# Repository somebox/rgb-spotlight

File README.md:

# RGB Spotlight

Status (2026-11-19): designed and released, not built yet. The driver is released as v2.4, the LED board as v2.0, a second LED board for 3.5 mm LEDs (`led35`) as v1.0, and the sheet-metal housing is in its eighth round. The first order, boards and housing for five lamps, was submitted to JLC on 2026-11-18: it is in JLC's reviews and not paid yet. The lenses were ordered on 2026-11-19. Every figure on this page is calculated or simulated; none is measured. Start with [HANDOVER.md](HANDOVER.md).

Chainable, addressable 3 x 3 W RGB spotlight for 12 V installations: three LEDs, red, green and blue, each behind its own lens, in a square aluminium housing with four barn doors, on a yoke. One lamp is one WS2811 pixel.

The pictures on this page are drawn from the design files. None is a photo.

- **v1** (EasyEDA, one FR4 board) was built but never lit: the PT4115 stages were wired as the wrong kind of buck, and the 74HC04 was unpowered.
- **v2** is a KiCad restart with two boards, an aluminium LED board and an FR4 driver board, and a housing designed around them.

| Document | What's in it |
| --- | --- |
| [HANDOVER.md](HANDOVER.md) | how we got here, decisions, the work remaining |
| [DESIGN.md](DESIGN.md) | requirements, the v1 post-mortem, numbered decisions, circuit, thermal estimate, simulation (§2.7), open items |
| [LAYOUT.md](LAYOUT.md) | the PCBs: floor plans, rules, scripted copper and routing, outline presets, checks |
| [mech/housing/](mech/housing/README.md) | the housing: sheet-metal parts, bought fasteners, assembly order, the scripts that build it and the files to order it from |
| [PRODUCTION.md](PRODUCTION.md) | order files, order checklist (polarity!), harness and bring-up, costs, the orders so far |
| [production/orders/2026-11-16-v2-first/](production/orders/2026-11-16-v2-first/ORDER.md) | the first order: the versions it pins, the parts to buy besides, its events |
| [docs/reviews/](docs/reviews/) | pre-order failure review: findings, bench list, firmware duties |
| [docs/index.html](docs/index.html) | the project's front page: what the lamp is, where it stands, links. GitHub Pages serves `docs/` at <https://somebox.github.io/rgb-spotlight/> |
| [docs/assembly/](docs/assembly/index.html) | assembly guide (HTML, open in a browser): the finished lamp, every part numbered, tools, and 14 steps with pictures drawn from the design files. Written before any part arrived: nothing in it is tried on hardware yet |

## What it does

A high-power, addressable RGB pixel for spotlights and creative lighting. It speaks the WS2811 protocol: 12 V and one data wire come in, and both go on to the next lamp.

The three colours are not mixed inside the lamp. Each LED has its own lens, 12 mm off the lamp's axis, and the colours meet on the wall. Where a door's edge cuts the beam, each colour is cut at a slightly different place, which leaves three colour bands along the shadow. That is the effect the design is after (DESIGN D8, D21–D23). How the bands look is not known until a lamp is built.

- **Optics:** three 20 mm PMMA TIR lenses, 30°, one over each LED.
  - They sit in one printed carrier (MJF PA12), and the hood clamps them by their flanges.
  - Four barn doors on the hood shape the beam, one pair at a time (D21, D22).
  - To compare, lenses of 15° and 45° and with beaded and frosted faces are ordered too, and two taller carriers to try the focus (D27).
- **Housing** ([mech/housing/](mech/housing/README.md)): sheet aluminium from JLCCNC, black powder coat.
  - A 65 mm square shell with vent slots, a back cap, an 84 mm square hood, and a yoke with two knobs.
  - About 94 mm long, 130 with the doors standing; about 0.38 kg (estimated).
  - The cap's back has two cut-outs for the connectors and four M3 threads for a box with a controller and a power supply (D31).
  - The yoke's base has one hole for a ¼ inch screw and two for M4.
- **Cooling:** passive. The LED board lies on a 3 mm aluminium plate. Behind it, eight spacers and four fins on three tie rods take the LEDs' heat to the air that passes the shell's slots.
- **LED board** (aluminium, 1 layer, 50 mm):
  - three XINGLIGHT HD2525 3 W LEDs (R/G/B), spread on a 12 mm-radius ring;
  - each LED on its own heat-spreading copper island;
  - six wire pads around a centre hole for the harness;
  - turned 45° in the housing, so each LED has its own height and its own place from left to right (D23).
- **Driver board** (FR4, 2 layers, 50 mm), on polyamide standoffs behind the fins, about 54 mm behind the LED board:
  - WS2811 pixel controller;
  - three PT4115 constant-current bucks (455 mA each);
  - level shifter on DIN, with a clamp for a feed voltage on the data pin (D28, D29, D34); Schmitt inverter for the PWM polarity;
  - 78L05 logic rail; TVS on the 12 V input.
- **Harness:** three wire pairs from the LED board through the 12 mm bore down the middle of the plate, spacers and fins, each on its own JST XH 2-pin plug (D33).
- **`led35`:** the LED board with pads for 3.5 mm LEDs, bought bare to try other colours on (D35).

The numbers are the assembly guide's part numbers: shell 1, cap 2, hood 3, plate 6, fins 7, spacers 8, carrier 9, LED board 10, driver 11, lenses 12, LED leads 13, tie studs 15, standoffs 18.

The LED board is drawn with a green mask; the ordered ones are white.

## Electrical specs

- **Supply:** 12 V (the PT4115 regulates down to about 6 V at the end of a chain)
- **Data:** WS2811 protocol, 800 kHz, single wire; 3.3 V or 5 V at DIN
- **LED current:** about 455 mA per channel (`I = 0.1 V / 0.22 Ω`); LEDs rated 1 A / 3 W
- **Full white:** 5.0 W, 0.42 A at 12 V per light (simulated, DESIGN.md §2.7); drivers about 80 % efficient
- **Chaining:** JST XH connectors (3 A) pass 12 V/GND through: up to 5 lights per 12 V feed, 2.2–2.6 A, with a 3 A fuse at the supply end (DESIGN.md §2.4, D14, D15). Use a 36 W supply for 4 lights and 60 W for 5, and add a feed per group after that.
- **Heat:** about 2.7 W in the LED board, which goes into the housing's heat plate and fins. About 0.9 W in the driver, mostly in the three Schottky diodes. See DESIGN.md §2.6–2.7.
- **Dimming:** brightness follows the 8-bit level within 5 % above 20 % and within 20 % down to 5 %. The lowest few levels are unreliable (DESIGN.md §2.7).
- **12 V on the data pin** (a mis-crimped cable, or the plug mated at an angle; review R6), simulated with up to 15 V there (D28, D29, `sim/results/data_cable.txt`). On the bench list.
  - With the light powered as well: the 5 V rail stays at 5.0 V and the level shifter's input at 5.43 V or less.
  - With the 12 V and data wires swapped, the light has no feed and the data pin alone holds the 5 V rail up: 2.9–3.5 V with 12 V on the pin, 3.7–4.4 V with 15 V. The level shifter's input stays at 4.84 V or less.
- **Firmware:** FastLED's `WS2811` (800 kHz) fits the WS2811's timing. ESPHome needs its timing set by hand (the review's firmware duties). WLED hasn't been checked. None of it has run on a lamp yet.

## Connections

| Connector | Where | Pins |
| --- | --- | --- |
| J1 IN | driver, back (JST XH 3, vertical) | 1 `12V`, 2 `DATA`, 3 `GND` |
| J2 OUT | driver, back (JST XH 3, vertical) | 1 `12V`, 2 `DATA`, 3 `GND` |
| J3 / J4 / J5 LED | driver, front (JST XH 2, vertical): red, green, blue | 1 `+`, 2 `-` |
| TP1–TP6 | LED board, around the centre hole | `R+` `R-` `G+` `G-` `B+` `B-`; solder the wires here, a pair to each socket |

J1 and J2 share one pin order, so chain with pin-1-to-pin-1 cables. v1 had J2 mirrored. In the housing, both are reached through the cap's cut-outs.

1. Connect the controller's data to J1 pin 2 of the first light, and +12 V / GND to pins 1 / 3. Keep controller and power grounds common.
2. Chain J2 of one light to J1 of the next.
3. Twist each colour's LED pair in the harness.

## Project layout

- `boards/led/`, `boards/driver/`: KiCad 10 projects. Schematics come from `scripts/sch_led.py` / `scripts/sch_driver.py`; boards from `scripts/make_led_pcb.sh` / `scripts/make_driver_pcb.sh`.
- `boards/led35/`: the LED board with pads for 3.5 mm LEDs (DESIGN D35), bought bare; `scripts/sch_led.py led35` and `scripts/make_led_pcb.sh led35`.
- `lib/`: project symbols, footprints and 3D models (`scripts/make_lib.py`).
- `scripts/`: generators and checks (`netcheck.py`, `ratsnest.py`, `make_previews.sh`, `make_fab.sh`); `pcbkit.toml` sets up pcb-kit's release and production record. The shared parts (schematic builder, silkscreen placer, DRC/ERC/board checks, previews, JLC fab files, ngspice runner) come from [pcb-kit](https://github.com/somebox/pcb-kit): `uv tool install -e ~/src/pcb-kit && pcbkit link`.
- `mech/housing/`: the housing as CadQuery scripts (`sheet.py`, then `round2.py` to `round8.py`, each changing the round before), its checks, and the STEP files and drawings to order from (`order6/`, `order7/`, `order8/`). Its [README](mech/housing/README.md) has the parts, the fasteners and the rebuild commands.
- `releases/<board>/v<version>/`: a release's order files and its frozen KiCad project, written by `pcbkit release` and never rewritten.
- `production/orders/<date>-<what>/`: an order's `order.toml` and the ORDER.md that `pcbkit production` writes from it.
- `sim/`: ngspice simulations of one LED channel (`channel.py`) and of the data link between two lights (`data_cable.py`), and the review's worst-case numbers (`worst_case.py`); tables and plots in `sim/results/`.
- `docs/previews/<board>/`: schematic PDF, board PNGs, 3D renders. `docs/previews/outline-presets.png` compares the board outline options.
- `docs/assembly/`, `docs/index.html`: the assembly guide and the front page. The guide's pictures come from `mech/housing/assembly_views.py`.
- **Board outline:** everything sits in a 50 mm core. The edge is a preset, `disc50` (current, and what the housing takes), `disc55`, `disc60` or `tabs3` (screw tabs). Change it with `scripts/set_outline.py`; see LAYOUT.md.
- `archive/v1-easyeda/`: the v1 EasyEDA exports, a KiCad import of the v1 board, its as-built netlist and the bodge guide.

Checks, previews and a release:

```bash
pcbkit erc boards/driver/driver.kicad_sch && python3 scripts/netcheck.py
pcbkit drc boards/driver/driver.kicad_pcb --save && pcbkit check boards/driver/driver.kicad_pcb
scripts/make_previews.sh all
pcbkit release --dry-run                                    # then pcbkit release: versioned order files in releases/ (PRODUCTION.md)
python3 sim/channel.py                                      # LED channel simulation
```

How the boards were generated. A released board is not regenerated: change it in place (LAYOUT.md, "Regenerating").

```bash
python3 scripts/sch_driver.py && python3 scripts/sch_led.py
scripts/make_led_pcb.sh && scripts/make_driver_pcb.sh --force --route
```

## BOM

- Driver: 22 lines, about $1.80 at qty 1 (bomi, 2026-11-17). JLC assembles 21 of them, 37 placements; J1 and J2 are soldered by hand. LED board: 3 lines, about $0.79 (bomi, 2026-11-14).
- The lenses, the fasteners and the other parts bought besides the boards are listed in [PRODUCTION.md](PRODUCTION.md), "Parts for the open orders".
- Each board has its own bomi project:

```bash
bomi --project boards/driver list --check
bomi --project boards/driver list --format markdown > docs/BOM_driver.md
bomi --project boards/led list --format markdown > docs/BOM_led.md
```

See [docs/BOM_driver.md](docs/BOM_driver.md), [docs/BOM_led.md](docs/BOM_led.md) and DESIGN.md §3. The v1 rationale doc is in `archive/v1-easyeda/rgb-spotlight-bom-v1.md`; its PT4115 connection tables are wrong.

## v1 (for reference)

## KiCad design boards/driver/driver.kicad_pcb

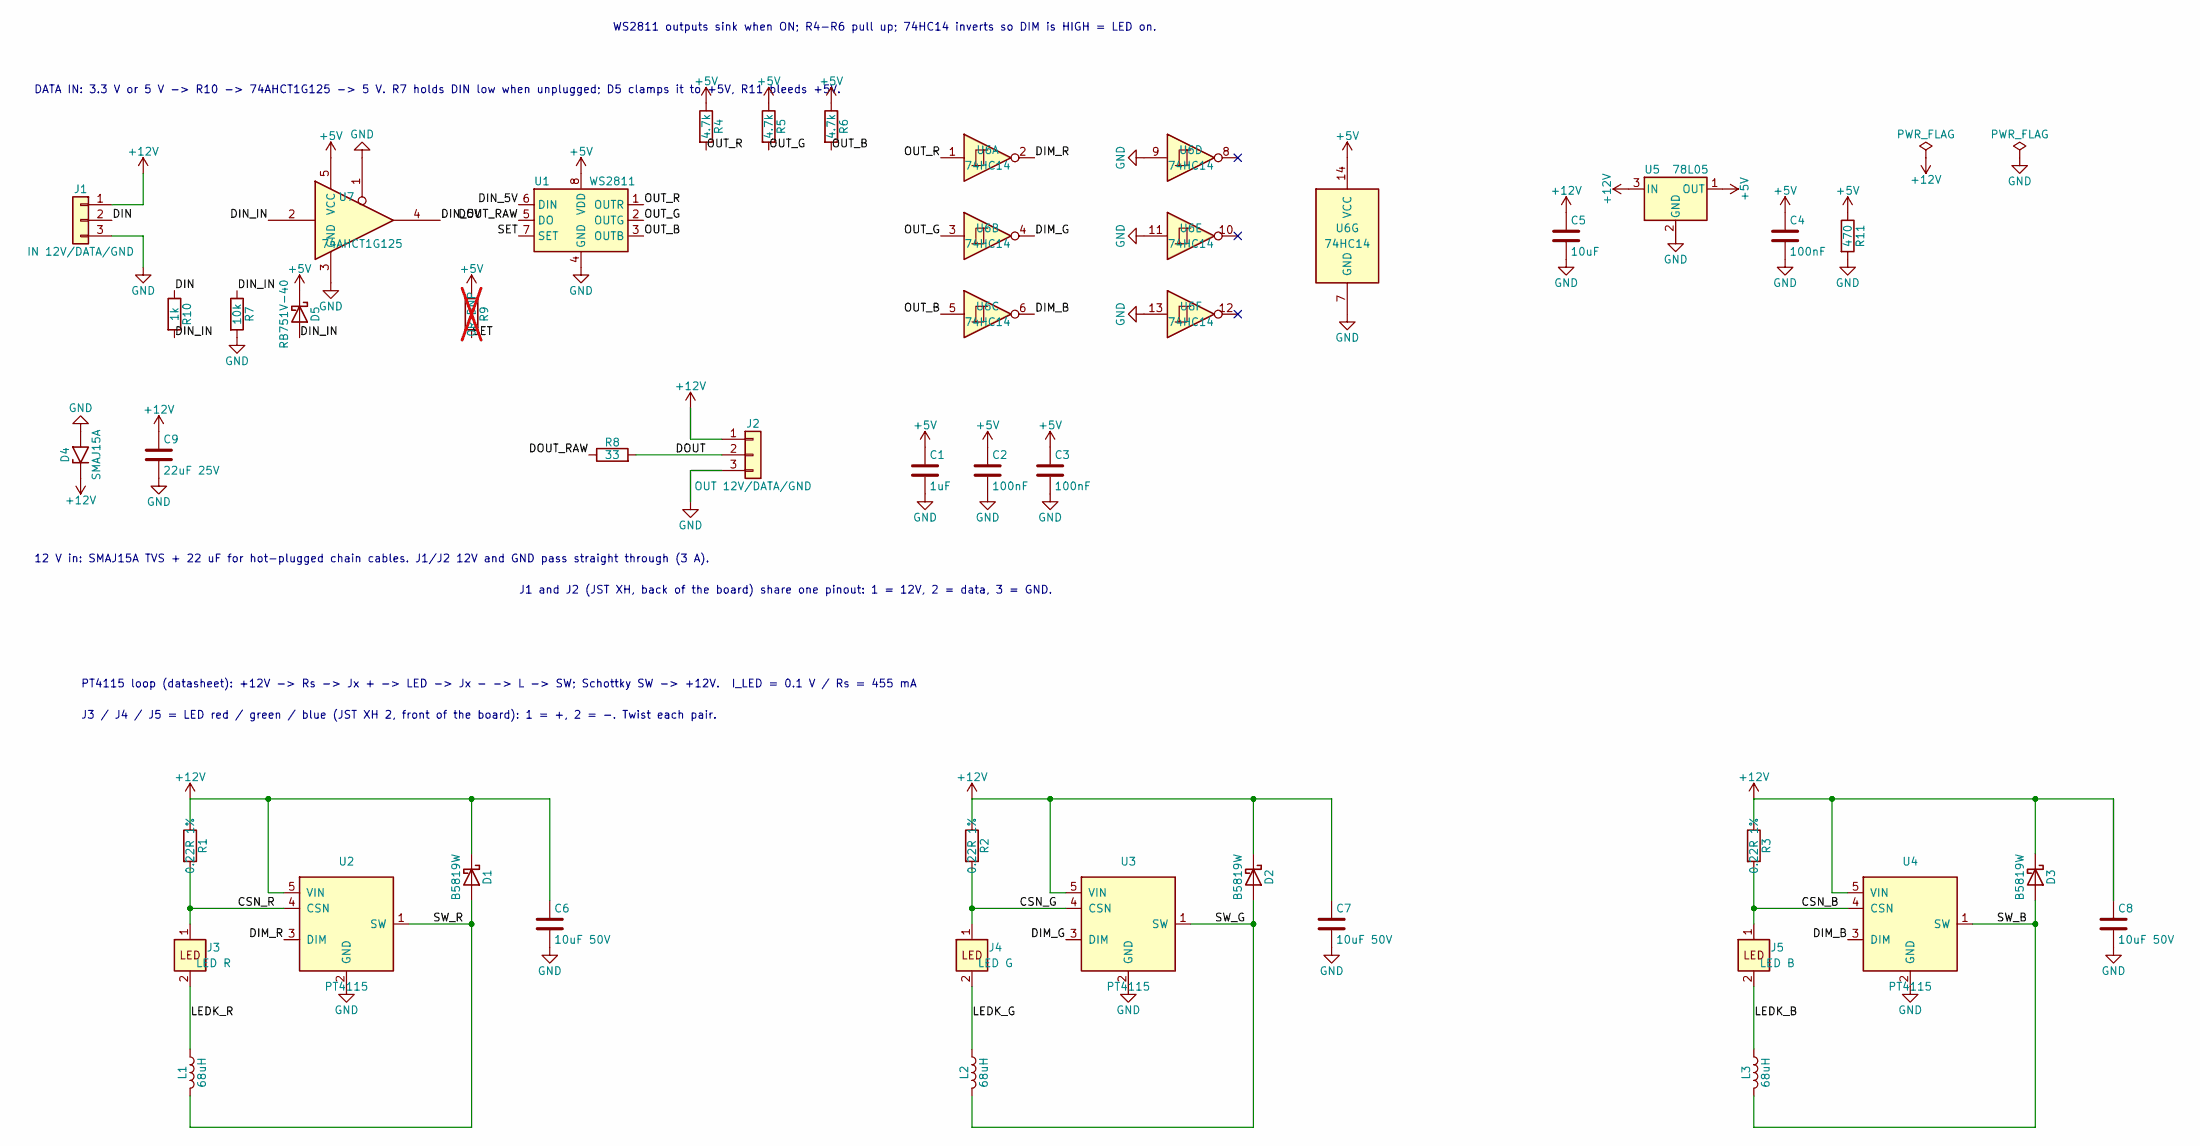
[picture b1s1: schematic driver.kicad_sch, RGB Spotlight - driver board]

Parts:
C1: 1uF; C_0402_1005Metric; LCSC C52923
C2, C3, C4: 100nF; C_0402_1005Metric; LCSC C1525
C5: 10uF; C_0805_2012Metric; LCSC C15850
C6, C7, C8: 10uF 50V; C_1206_3216Metric; MPN CL31A106KBHNNNE; LCSC C13585
C9: 22uF 25V; C_1206_3216Metric; MPN CL31A226KAHNNNE; LCSC C12891
D1, D2, D3: B5819W; D_SOD-123; LCSC C64885
D4: SMAJ15A; D_SMA; LCSC C19077535
D5: RB751V-40; D_SOD-323; MPN RB751V-40; LCSC C7502691
J1: IN 12V/DATA/GND; JST_XH_B3B-XH-A_1x03_P2.50mm_Vertical; MPN B3B-XH-A(LF)(SN); LCSC C144394
J2: OUT 12V/DATA/GND; JST_XH_B3B-XH-A_1x03_P2.50mm_Vertical; MPN B3B-XH-A(LF)(SN); LCSC C144394
J3: LED R; JST_XH_B2B-XH-A_1x02_P2.50mm_Vertical; MPN B2B-XH-A(LF)(SN); LCSC C158012
J4: LED G; JST_XH_B2B-XH-A_1x02_P2.50mm_Vertical; MPN B2B-XH-A(LF)(SN); LCSC C158012
J5: LED B; JST_XH_B2B-XH-A_1x02_P2.50mm_Vertical; MPN B2B-XH-A(LF)(SN); LCSC C158012
L1, L2, L3: 68uH; L_Changjiang_FNR6045S; MPN FNR6045S680MT; LCSC C168091
R1, R2, R3: 0.22R 1%; R_1206_3216Metric; MPN FRL1206FR220TS; LCSC C2907349
R4, R5, R6: 4.7k; R_0402_1005Metric; LCSC C25900
R7: 10k; R_0402_1005Metric; LCSC C25744
R8: 33; R_0402_1005Metric; LCSC C25105
R9: 0R DNP; R_0402_1005Metric; not fitted
R10: 1k; R_0402_1005Metric; LCSC C427241
R11: 470; R_0603_1608Metric; MPN 0603WAF4700T5E; LCSC C23179
U1: WS2811; SOIC-8_3.9x4.9mm_P1.27mm; LCSC C114581
U2, U3, U4: PT4115; SOT-89-5; LCSC C347356
U5: 78L05; SOT-89-3; MPN 78L05G-AB3-R; LCSC C71136
U6: 74HC14; SOIC-14_3.9x8.7mm_P1.27mm; MPN 74HC14D,653; LCSC C5605
U7: 74AHCT1G125; SOT-353_SC-70-5; MPN SN74AHCT1G125DCKR; LCSC C350557

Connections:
+5V: C1.1, C2.1, C3.1, C4.1, D5.1 (K), R4.1, R5.1, R6.1, R9.1, R11.1, U1.8 (VDD), U5.1 (OUT), U6.14 (VCC), U7.5 (VCC)
+12V: C5.1, C6.1, C7.1, C8.1, C9.1, D1.1 (K), D2.1 (K), D3.1 (K), D4.1 (A1), J1.1, J2.1, R1.1, R2.1, R3.1, U2.5 (VIN), U3.5 (VIN), U4.5 (VIN), U5.3 (IN)
/CSN_B: J5.1 (+), R3.2, U4.4 (CSN)
/CSN_G: J4.1 (+), R2.2, U3.4 (CSN)
/CSN_R: J3.1 (+), R1.2, U2.4 (CSN)
/DIM_B: U4.3 (DIM), U6.6
/DIM_G: U3.3 (DIM), U6.4
/DIM_R: U2.3 (DIM), U6.2
/DIN: J1.2, R10.1
/DIN_5V: U1.6 (DIN), U7.4
/DIN_IN: D5.2 (A), R7.1, R10.2, U7.2
/DOUT: J2.2, R8.2
/DOUT_RAW: R8.1, U1.5 (DO)
/LEDK_B: J5.2 (-), L3.1
/LEDK_G: J4.2 (-), L2.1
/LEDK_R: J3.2 (-), L1.1
/OUT_B: R6.2, U1.3 (OUTB), U6.5
/OUT_G: R5.2, U1.2 (OUTG), U6.3
/OUT_R: R4.2, U1.1 (OUTR), U6.1
/SET: R9.2, U1.7 (SET)
/SW_B: D3.2 (A), L3.2, U4.1 (SW)
/SW_G: D2.2 (A), L2.2, U3.1 (SW)
/SW_R: D1.2 (A), L1.2, U2.1 (SW)
GND: C1.2, C2.2, C3.2, C4.2, C5.2, C6.2, C7.2, C8.2, C9.2, D4.2 (A2), J1.3, J2.3, R7.2, R11.2, U1.4 (GND), U2.2 (GND), U3.2 (GND), U4.2 (GND), U5.2 (GND), U6.7 (GND), U6.9, U6.11, U6.13, U7.1, U7.3 (GND)

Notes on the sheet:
DATA IN: 3.3 V or 5 V -> R10 -> 74AHCT1G125 -> 5 V. R7 holds DIN low when unplugged; D5 clamps it to +5V, R11 bleeds +5V.
12 V in: SMAJ15A TVS + 22 uF for hot-plugged chain cables. J1/J2 12V and GND pass straight through (3 A).
WS2811 outputs sink when ON; R4-R6 pull up; 74HC14 inverts so DIM is HIGH = LED on.
J1 and J2 (JST XH, back of the board) share one pinout: 1 = 12V, 2 = data, 3 = GND.
PT4115 loop (datasheet): +12V -> Rs -> Jx + -> LED -> Jx - -> L -> SW; Schottky SW -> +12V. I_LED = 0.1 V / Rs = 455 mA
J3 / J4 / J5 = LED red / green / blue (JST XH 2, front of the board): 1 = +, 2 = -. Twist each pair.

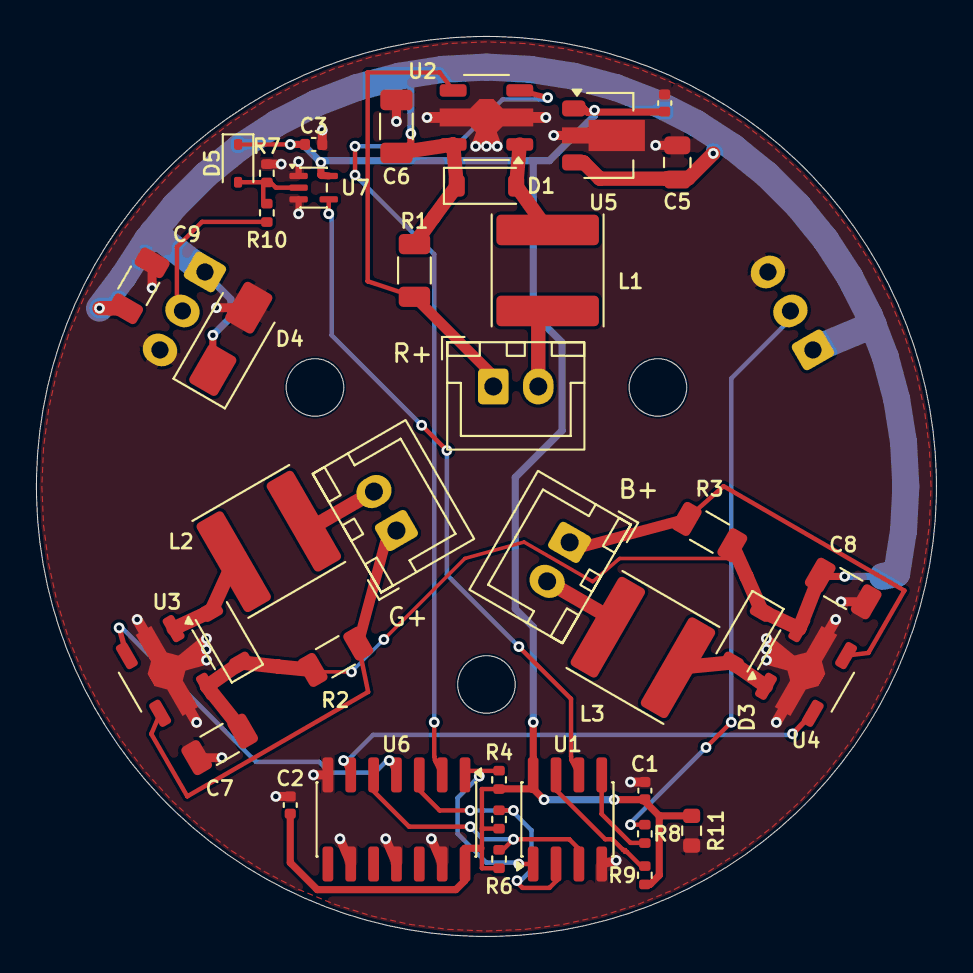
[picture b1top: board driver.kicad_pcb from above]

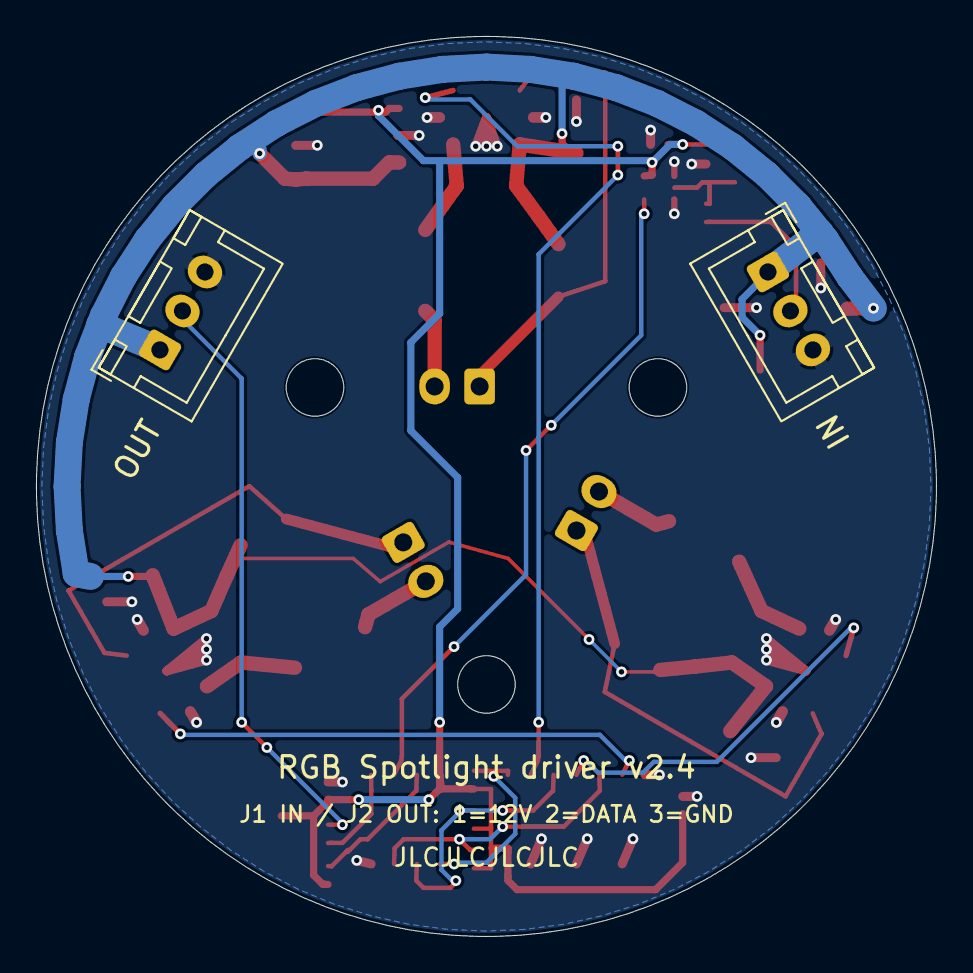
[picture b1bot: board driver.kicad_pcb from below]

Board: 2 copper layers, 50.0 x 50.0 mm, 43 parts (2 on the bottom side), 24 nets.

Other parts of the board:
H1, H2, H3: M3; MountingHole_3.2mm_M3

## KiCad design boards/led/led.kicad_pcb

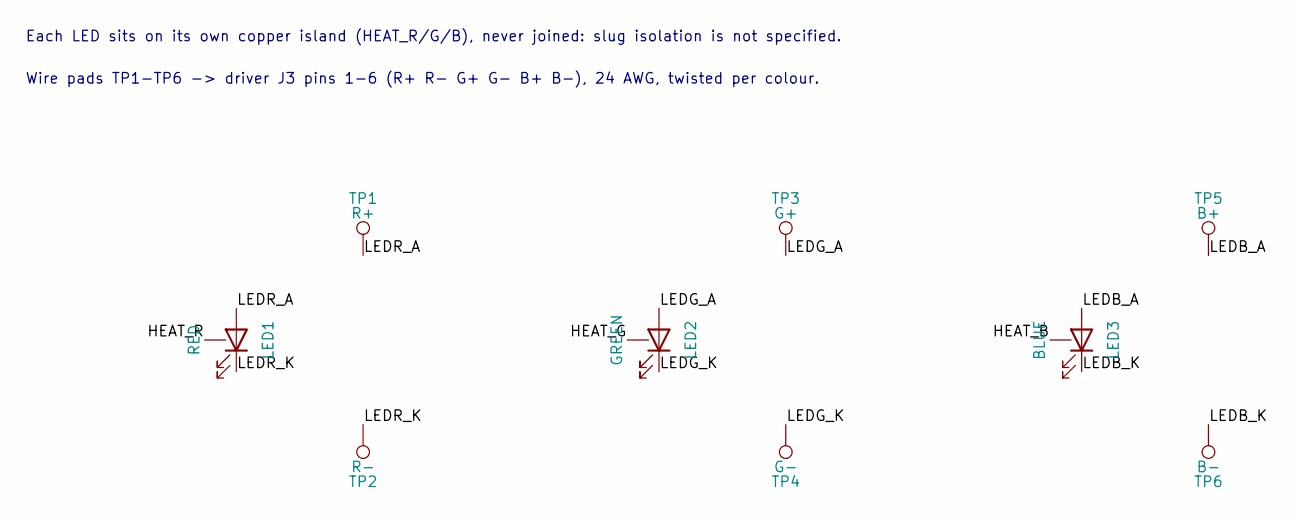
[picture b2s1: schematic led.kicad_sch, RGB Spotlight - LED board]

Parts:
LED1: RED; LED_XINGLIGHT_HD2525; MPN XL-HD2525SURC-A4; LCSC C49237857
LED2: GREEN; LED_XINGLIGHT_HD2525; MPN XL-HD2525UGC-A4; LCSC C49237859
LED3: BLUE; LED_XINGLIGHT_HD2525; MPN XL-HD2525UBC-A4; LCSC C49237860
TP1: R+; WirePad_2.2x3.5mm
TP2: R-; WirePad_2.2x3.5mm
TP3: G+; WirePad_2.2x3.5mm
TP4: G-; WirePad_2.2x3.5mm
TP5: B+; WirePad_2.2x3.5mm
TP6: B-; WirePad_2.2x3.5mm

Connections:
/HEAT_B: LED3.3 (PAD)
/HEAT_G: LED2.3 (PAD)
/HEAT_R: LED1.3 (PAD)
/LEDB_A: LED3.2 (A), TP5.1
/LEDB_K: LED3.1 (K), TP6.1
/LEDG_A: LED2.2 (A), TP3.1
/LEDG_K: LED2.1 (K), TP4.1
/LEDR_A: LED1.2 (A), TP1.1
/LEDR_K: LED1.1 (K), TP2.1

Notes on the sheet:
Each LED sits on its own copper island (HEAT_R/G/B), never joined: slug isolation is not specified.
Wire pads TP1-TP6 -> driver J3 pins 1-6 (R+ R- G+ G- B+ B-), 24 AWG, twisted per colour.

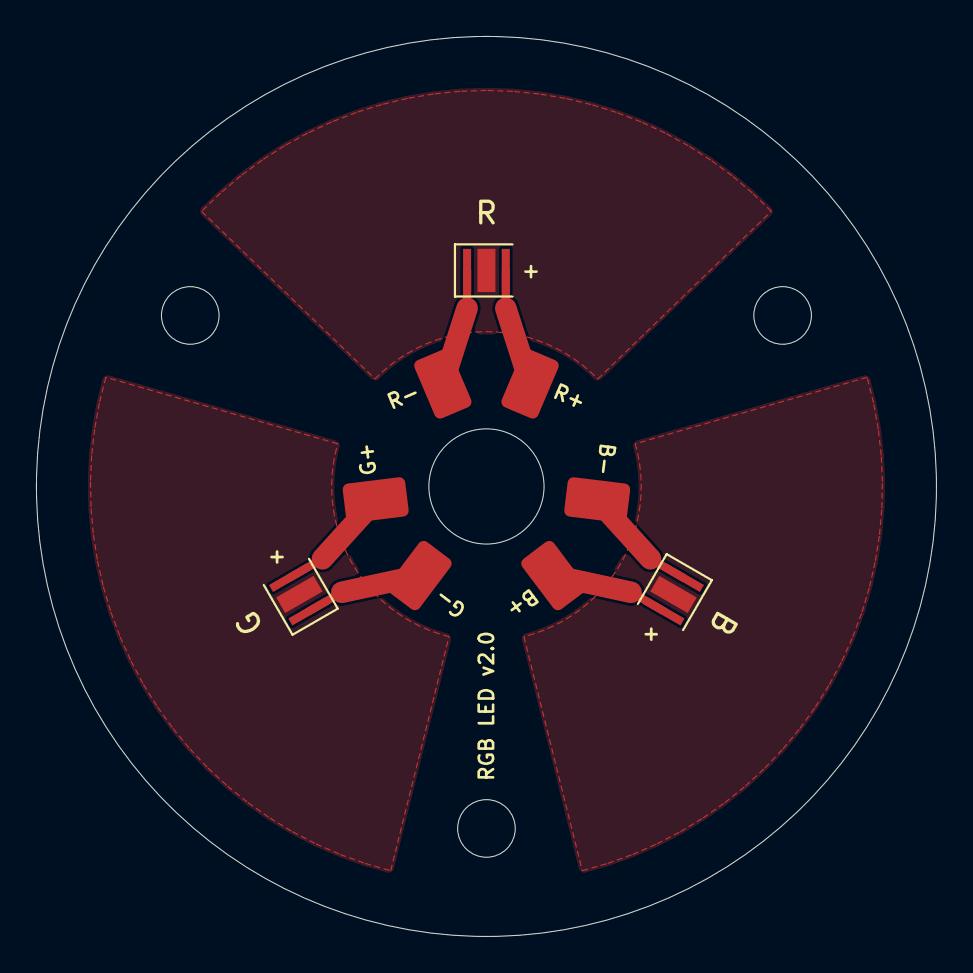
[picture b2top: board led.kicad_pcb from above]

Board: 2 copper layers, 50.0 x 50.0 mm, 12 parts (0 on the bottom side), 6 nets.

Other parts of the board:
H1, H2, H3: M3; MountingHole_3.2mm_M3

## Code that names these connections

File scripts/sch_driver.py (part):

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comps = [
    # ---- data in: J1 -> R10 1k -> (R7 10k pull-down) -> 74AHCT1G125 (3.3 V -> 5 V) -> WS2811 DIN
    dict(ref="J1", lib="Connector_Generic:Conn_01x03", val="IN 12V/DATA/GND", fp=XH3, x=30.48, y=60.96, mirror="y",
         lcsc="C144394", fields={"MPN": "B3B-XH-A(LF)(SN)"}, pins={"1": None, "2": "DIN", "3": None}),
    r("R10", "1k", "C427241", 45.72, 76.2, "DIN", "DIN_IN"),  # 1k limits the clamp current when DIN rings below GND (D18); a 200 mW 0402,
                                                               # for the 66-118 mW of a feed voltage held on the pin (D34, DESIGN 2.2)
    r("R7", "10k", "C25744", 55.88, 76.2, "DIN_IN", "GND"),
    dict(ref="U7", lib="74xGxx:74AHCT1G125", val="74AHCT1G125", fp="Package_TO_SOT_SMD:SOT-353_SC-70-5",
         x=76.2, y=60.96, lcsc="C350557", fields={"MPN": "SN74AHCT1G125DCKR"},
         pins={"1": "GND", "2": "DIN_IN", "3": "GND", "4": "DIN_5V", "5": "+5V"}),
    # ---- 12 V input protection (hot-plugged chain cables): TVS + bulk
    dict(ref="D4", lib="Diode:SMAJ15A", val="SMAJ15A", fp="Diode_SMD:D_SMA", x=30.48, y=99.06, rot=90, lcsc="C19077535",
         pins={"1": "+12V", "2": "GND"}),
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    # ---- WS2811: open-drain outputs, pulled up to 5 V, inverted by the 74HC14 (DESIGN.md §2.3)
    dict(ref="U1", lib="Driver_LED:WS2811", val="WS2811", fp="Package_SO:SOIC-8_3.9x4.9mm_P1.27mm",
         x=111.76, y=60.96, lcsc="C114581",
         pins={"1": "OUT_R", "2": "OUT_G", "3": "OUT_B", "4": "GND", "5": "DOUT_RAW", "6": "DIN_5V", "7": "SET", "8": "+5V"}),
    r("R9", "0R DNP", "", 93.98, 76.2, "+5V", "SET"),   # SET strap, unfitted: Worldsemi V2.2 says NC, older/clone WS2811s use it for 400/800k
    r("R4", "4.7k", "C25900", 132.08, 45.72, "+5V", "OUT_R"),
    r("R5", "4.7k", "C25900", 142.24, 45.72, "+5V", "OUT_G"),
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         lcsc="C144394", fields={"MPN": "B3B-XH-A(LF)(SN)"}, pins={"1": None, "2": None, "3": None}),
    # ---- 74HC14 (Schmitt inputs for the WS2811's slow edges, D17): gates 1-3 invert OUT_x -> DIM_x; gates 4-6 inputs to GND, outputs open; unit 7 = power
    dict(ref="U6", unit=1, lib="74xx:74HC14", val="74HC14", fp="Package_SO:SOIC-14_3.9x8.7mm_P1.27mm",
         x=177.8, y=50.8, lcsc="C5605", fields={"MPN": "74HC14D,653"}, pins={"1": "OUT_R", "2": "DIM_R"}),
    dict(ref="U6", unit=2, lib="74xx:74HC14", x=177.8, y=63.5, pins={"3": "OUT_G", "4": "DIM_G"}),
    dict(ref="U6", unit=3, lib="74xx:74HC14", x=177.8, y=76.2, pins={"5": "OUT_B", "6": "DIM_B"}),
    dict(ref="U6", unit=4, lib="74xx:74HC14", x=210.82, y=50.8, pins={"9": "GND", "8": "NC"}),
    dict(ref="U6", unit=5, lib="74xx:74HC14", x=210.82, y=63.5, pins={"11": "GND", "10": "NC"}),
    dict(ref="U6", unit=6, lib="74xx:74HC14", x=210.82, y=76.2, pins={"13": "GND", "12": "NC"}),
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    ]

# ---- D5 after the channels, so the power symbols numbered before it keep their numbers.
#      DIN_IN clamp to +5V: U7's input is rated to 7 V with no clamp above it, so 12 V on the data pin (a mis-crimped
#      cable) would leave ~10.9 V there; D5 holds it near 5.4 V, R10 limiting the current to ~6 mA (D28).
comps.append(dict(ref="D5", lib="Device:D_Schottky", val="RB751V-40", fp="Diode_SMD:D_SOD-323", x=66.04, y=76.2, rot=270,
                  lcsc="C7502691", fields={"MPN": "RB751V-40"}, pins={"1": "+5V", "2": "DIN_IN"}))
# ---- R11 last, for the same reason. The 78L05 can't sink current, so D5's current would lift the +5V rail (to 6.5-10 V
#      at 12 V on the pin); R11 draws 10.6 mA, more than the pin can push in up to 15 V, so the 78L05 stays in control (D29).
#      0603 for its 53 mW.
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
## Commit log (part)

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2026-03-28 update bom to use https://github.com/somebox/bomi for part tracking
2026-04-19 Update README.md to reflect changes in RGB spotlight specifications, including size, electrical specs, and connection details. Improved clarity and organization of content.
